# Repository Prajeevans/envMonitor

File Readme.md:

# Mini Environmental Monitoring PCB

A mini environmental monitoring system designed using **KiCad 10** and an **Arduino Nano**. This project monitors temperature and ambient light intensity and provides an interface for an OLED display and LED indicators.

## Features

- Temperature sensing using an LM35 temperature sensor
- Ambient light detection using a Light Dependent Resistor (LDR)
- OLED display interface using I²C communication
- LED status indicators controlled by the Arduino Nano
- Custom electronic schematic design
- Custom PCB layout and routing
- Power and ground planning
- Electrical Rules Check (ERC) and Design Rules Check (DRC)

## Components Used

| Component | Purpose |
|---|---|
| Arduino Nano | Main controller |
| LM35 temperature sensor | Measures temperature |
| Light Dependent Resistor (LDR) | Detects ambient light intensity |
| OLED display connector | Connects the OLED display |
| LEDs | Visual status indication |
| 330 Ω resistors | Limit LED current |
| 10 kΩ resistor | LDR voltage divider |
| 100 nF capacitor | Power supply decoupling |
| 10 µF capacitor | Power supply filtering |

## Tools and Technologies

- **KiCad 10** — Schematic design and PCB layout
- **Arduino Nano** — Embedded controller
- **Electronic Circuit Design** — Component selection and circuit connections
- **PCB Design** — Component placement, track routing, and design verification

## Circuit Schematic

The circuit schematic illustrates the electrical connections between the Arduino Nano, LM35 temperature sensor, LDR voltage divider, OLED connector, LEDs, resistors, and capacitors.

## PCB Layout

The PCB layout illustrates the physical arrangement of the electronic components and the copper tracks connecting them.

## Design Verification

- [x] Schematic design completed
- [x] Electrical Rules Check (ERC)
- [x] Component footprint assignment and verification
- [x] PCB component placement
- [x] PCB track routing
- [x] Design Rule Check (DRC)

## Project Status

The schematic and PCB design were developed using KiCad 10. Hardware testing and firmware development can be documented separately as those stages are completed.

## Future Improvements

- Develop Arduino firmware for temperature and light measurements
- Display real-time sensor readings on the OLED display
- Calibrate and evaluate sensor accuracy
- Test the assembled PCB under different environmental conditions
- Improve the design based on testing results

## Learning Objectives

- Understand electronic schematic design
- Learn component selection and footprint assignment
- Practice PCB component placement and track routing
- Apply power and ground planning principles
- Perform ERC and DRC checks
- Develop practical PCB design skills

---

**Designed using KiCad 10.**

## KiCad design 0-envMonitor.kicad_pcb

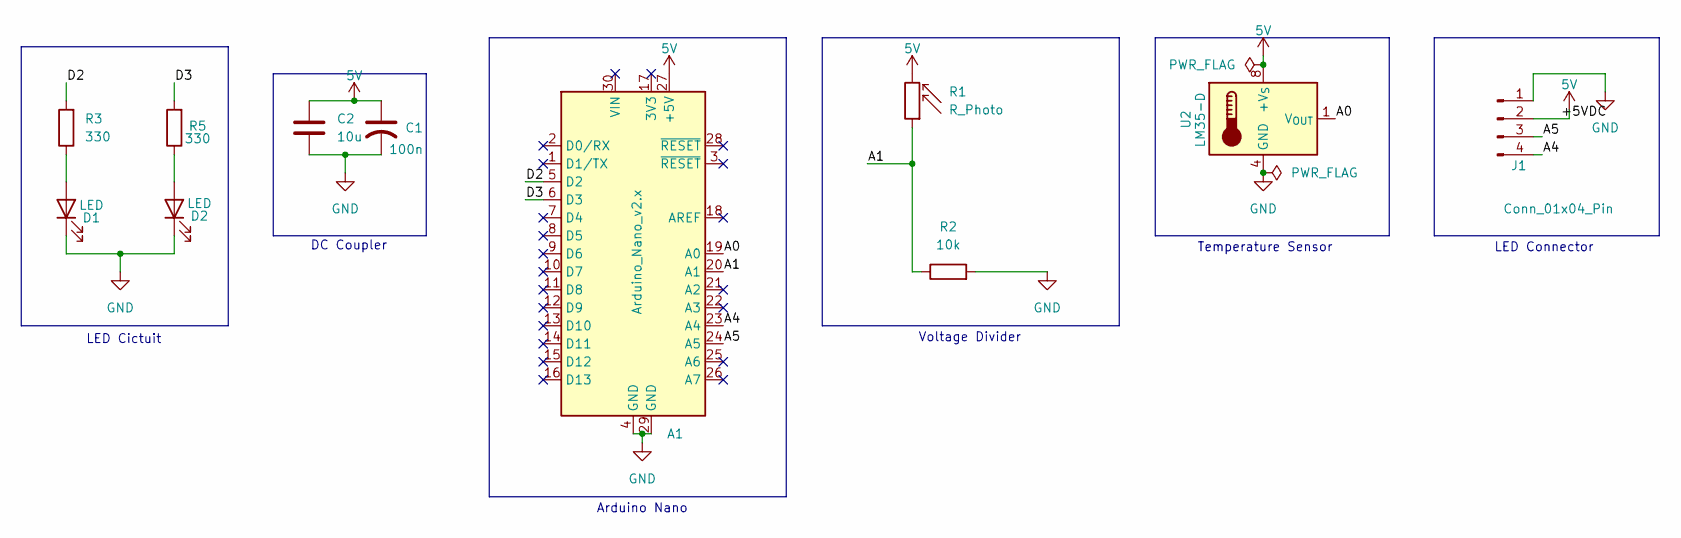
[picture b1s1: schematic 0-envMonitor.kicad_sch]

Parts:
A1: Arduino_Nano_v2.x; Arduino_Nano
C1: 100n
C2: 10u
D1, D2: LED
J1: Conn_01x04_Pin
R1: R_Photo
R2: 10k
R3, R5: 330
U2: LM35-D; SOIC-8_3.9x4.9mm_P1.27mm

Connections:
5V: A1.27 (+5V), C1.1, C2.1, J1.2, R1.2, U2.8 (+V_{S})
/A0: A1.19 (A0), U2.1 (V_{OUT})
/A1: A1.20 (A1), R1.1, R2.1
/A4: A1.23 (A4), J1.4
/A5: A1.24 (A5), J1.3
/D2: A1.5 (D2), R3.2
/D3: A1.6 (D3), R5.2
GND: A1.4 (GND), A1.29 (GND), C1.2, C2.2, D1.1 (K), D2.1 (K), J1.1, R2.2, U2.4 (GND)
unnamed: D1.2 (A), R3.1
unnamed: D2.2 (A), R5.1

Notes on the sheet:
LED Connector
Voltage Divider
DC Coupler
Temperature Sensor
LED Cictuit
Arduino Nano

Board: 2 copper layers, 11 parts (0 on the bottom side), 10 nets, no tracks yet.
